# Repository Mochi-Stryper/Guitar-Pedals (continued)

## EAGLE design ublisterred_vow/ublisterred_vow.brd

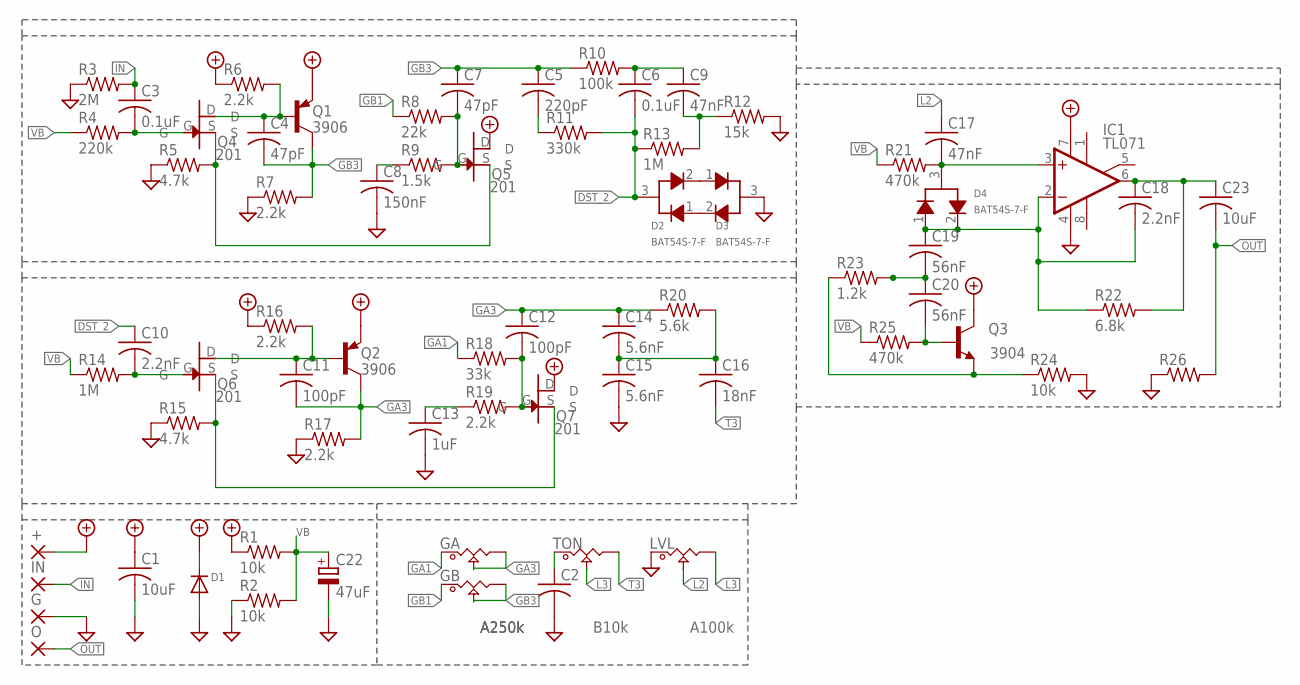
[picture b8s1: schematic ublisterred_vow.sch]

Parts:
+: SMD2; SMD1,27-2,54
C1, C23: 10uF; C1206
C2: C-USC0603; C0603
C3, C6: 0.1uF; C0603
C4, C7: 47pF; C0603
C5: 220pF; C0603
C8: 150nF; C0603
C9, C17: 47nF; C0603
C10, C18: 2.2nF; C0603
C11, C12: 100pF; C0603
C13: 1uF; C0603
C14, C15: 5.6nF; C0603
C16: 18nF; C0603
C19, C20: 56nF; C0603
C22: 47uF; CAPMP7343X310N
D1: DIODESOD-123; SOD-123
D2, D3, D4: BAT54S-7-F; SOT23-3
G: SMD2; SMD1,27-2,54
GA: A250k; POT_9MM_SMD
GB: A250k; POT_9MM_SMD
IC1: TL071; SO08
IN: SMD2; SMD1,27-2,54
LVL: A100k; POT_9MM_SMD
O: SMD2; SMD1,27-2,54
Q1, Q2: 3906; SOT23-3
Q3: 3904; SOT23-3
Q4, Q5, Q6, Q7: 201; MMBFJ201
R1, R2, R24: 10k; R0603
R3: 2M; R0603
R4: 220k; R0603
R5, R15: 4.7k; R0603
R6, R7, R16, R17, R19: 2.2k; R0603
R8: 22k; R0603
R9: 1.5k; R0603
R10: 100k; R0603
R11: 330k; R0603
R12: 15k; R0603
R13, R14: 1M; R0603
R18: 33k; R0603
R20: 5.6k; R0603
R21, R25: 470k; R0603
R22: 6.8k; R0603
R23: 1.2k; R0603
R26: R-US_R0603; R0603
TON: B10k; POT_9MM_SMD

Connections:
+9V: +.1, C1.1, D1.C, IC1.7 (V+), Q1.2 (E), Q2.2 (E), Q3.3 (C), Q5.D, Q7.D, R1.1, R6.1, R16.1
DST_2: C6.2, C10.1, D2.3, R11.2, R13.1
GA1: GA.1, R18.1
GA3: C11.2, C12.1, C14.1, GA.2, GA.3, Q2.3 (C), R17.2, R20.1
GB1: GB.1, R8.1
GB3: C4.2, C5.1, C7.1, GB.2, GB.3, Q1.3 (C), R7.2, R10.1
GND: C1.2, C2.2, C8.2, C13.2, C15.2, C22.2 (-), D1.A, D3.3, G.1, IC1.4 (V-), LVL.1, R2.1, R3.1, R5.1, R7.1, R12.2, R15.1, R17.1, R24.2, R26.1
IN: C3.1, IN.1, R3.2
L2: C17.1, LVL.2
L3: LVL.3, TON.2
unnamed: C4.1, Q1.1 (B), Q4.D, R6.2
unnamed: C3.2, Q4.G, R4.2
unnamed: Q4.S, Q5.S, R5.2
unnamed: C7.2, Q5.G, R8.2, R9.2
unnamed: C2.1, TON.1
unnamed: C8.1, R9.1
unnamed: C5.2, R11.1
unnamed: C6.1, C9.1, R10.2
unnamed: C10.2, Q6.G, R14.2
unnamed: C9.2, R12.1, R13.2
unnamed: D2.2, D3.1
unnamed: D2.1, D3.2
unnamed: Q6.S, Q7.S, R15.2
unnamed: C11.1, Q2.1 (B), Q6.D, R16.2
unnamed: C12.2, Q7.G, R18.2, R19.2
unnamed: C13.1, R19.1
unnamed: C14.2, C15.1, C16.1, R20.2
unnamed: C17.2, D4.3, IC1.3 (+IN), R21.2
unnamed: C18.2, C19.1, D4.1, D4.2, IC1.2 (-IN), R22.1
unnamed: C18.1, C23.1, IC1.6 (OUT), R22.2
unnamed: C19.2, C20.1, R23.2
unnamed: C20.2, Q3.1 (B), R25.2
unnamed: Q3.2 (E), R23.1, R24.1
OUT: C23.2, O.1, R26.2
T3: C16.2, TON.3
VB: C22.1 (+), R1.2, R2.2, R4.1, R14.1, R21.1, R25.1

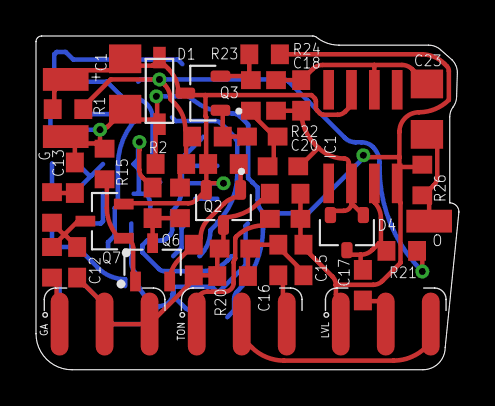
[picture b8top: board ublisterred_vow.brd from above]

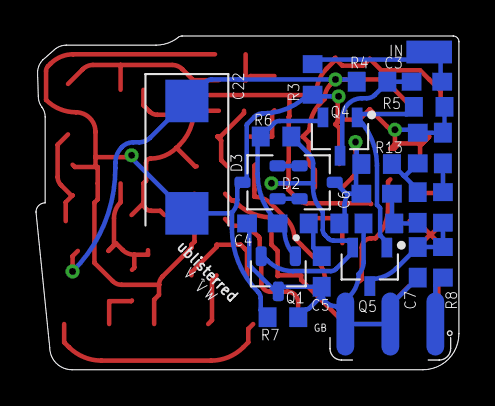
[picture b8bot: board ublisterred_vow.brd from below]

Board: 2 copper layers, 23.5 x 18.5 mm, 68 parts (26 on the bottom side), 36 nets.
